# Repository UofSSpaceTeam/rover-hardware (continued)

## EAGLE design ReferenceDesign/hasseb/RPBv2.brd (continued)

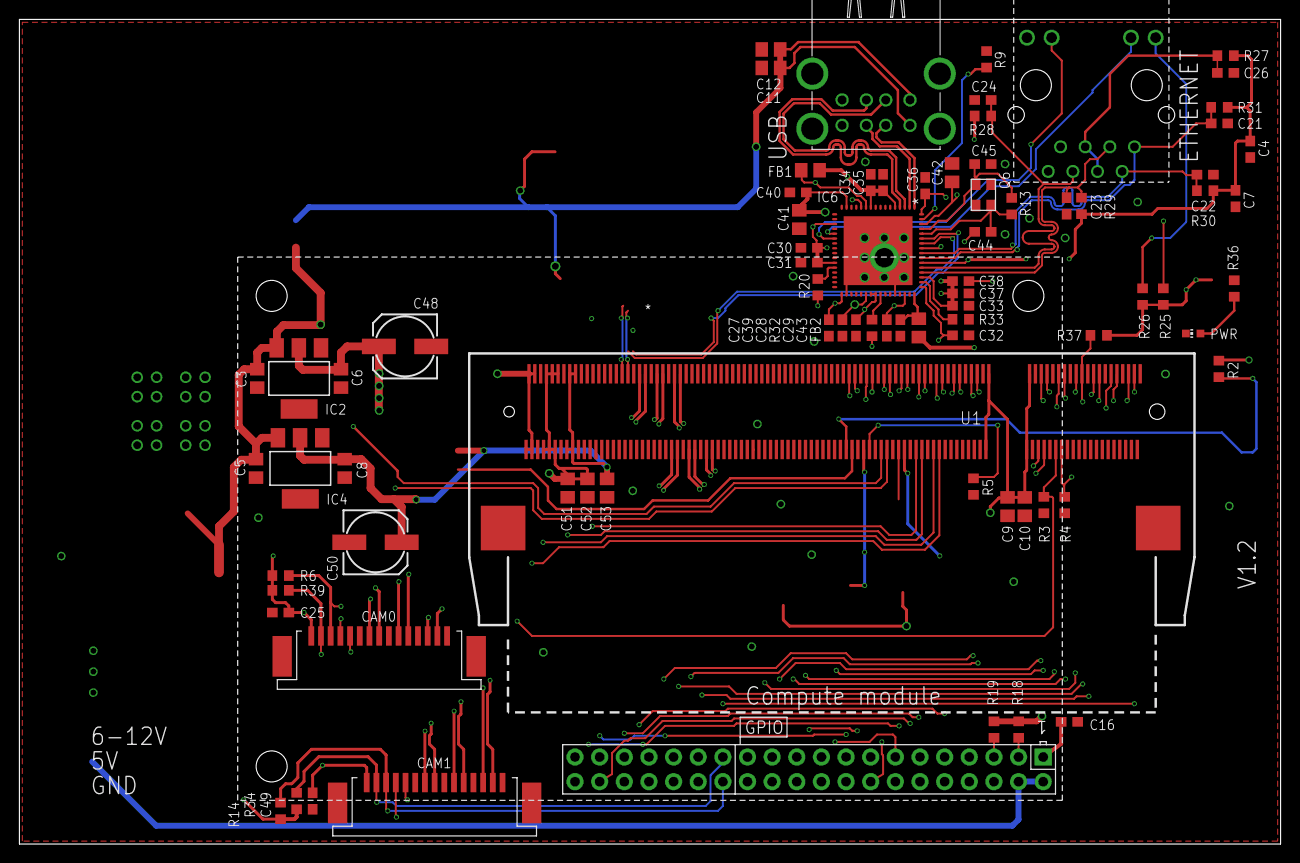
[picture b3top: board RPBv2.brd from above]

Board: 4 copper layers, 130.0 x 85.0 mm, 79 parts (0 on the bottom side), 76 nets.

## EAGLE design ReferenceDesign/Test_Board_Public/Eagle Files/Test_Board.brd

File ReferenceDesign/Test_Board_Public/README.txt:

----This Zip File has been downloaded from http://rpi.pmfg.me

----If you bought these plans from another location other than http://rpi.pmfg.me 
    please get a refund. 

---If you do like the Test Board Please Donate on http://rpi.pmfg.me

---If you do use this Test Board in a Commercial Product. 
   Please Donate from the sales of your product. 
   the world and I will Love you for it.

---This board Comprises of a 4 Layer Board. do not go less than 4 Layers.
   Please see /Eagle Files/Layers_Info.jpg on how the layers should be set. 
   This Must be Accurate as USB and Ethernet Traces have been set to use those Layer settings.

---Please note that the Test Board in its CURRENT Configuration will work!
   This Board has been Tested Extensively before the plans have been made available on the Internet.

---These Plans have been Provided AS IS and As such I will hold no Responsibility if they have been changed
   or an Issue arise from PCB manufacturing or Materials.

---Lastly Please put a mention about me on any product 
   that was derived from this Test Board. 

---if you have any Questions or Queries please post them to the link below. 
   http://www.raspberrypi.org/forums/viewtopic.php?f=98&t=80708

Thank You!

This zip file should contain:
  README.txt (this file)
  /Eagle Files/Test_Board.sch (Eagle CAD Schematic)
  /Eagle Files/Test_Board.brd (Eagle CAD Board File)
  /Eagle Files/Test_Board_BOM.xlsx (Bill of Materials)
  Test_Board_Schematic.pdf (PDF of schematic)
  /GERBERS (Board gerbers)

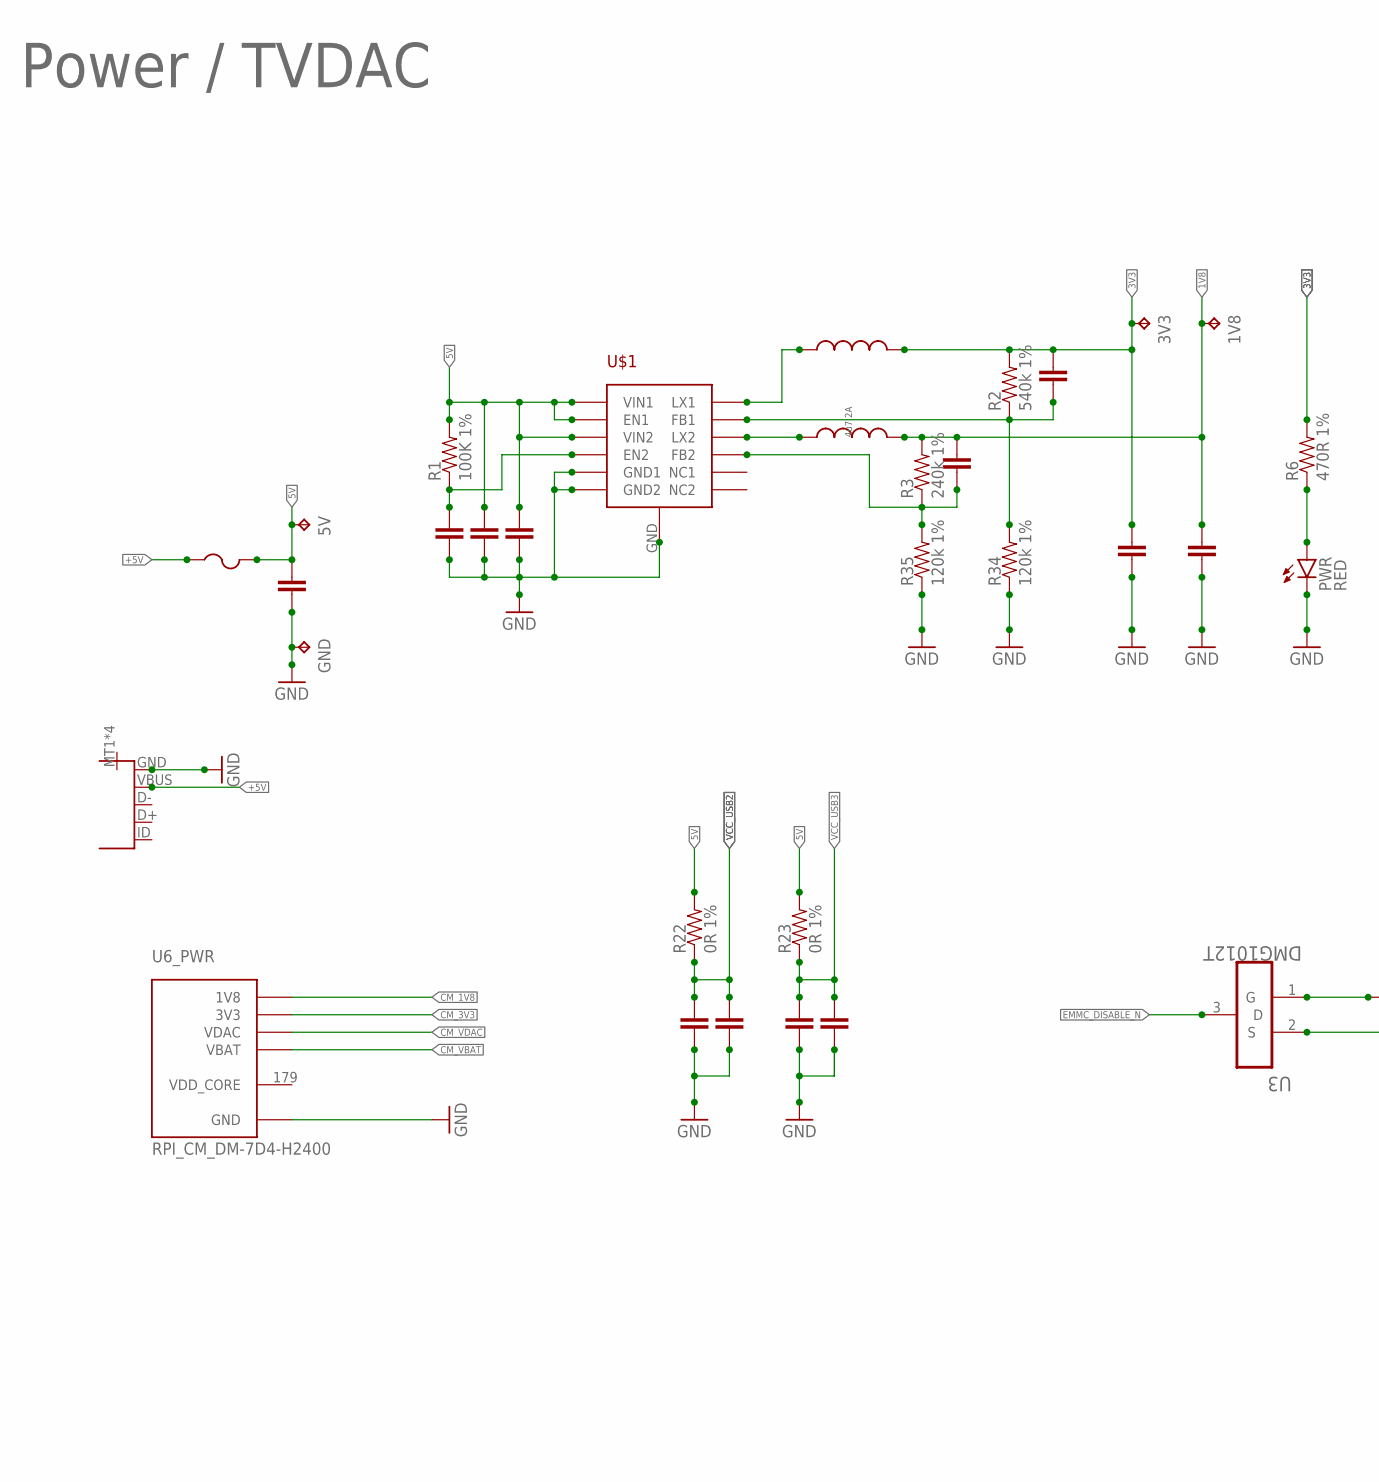
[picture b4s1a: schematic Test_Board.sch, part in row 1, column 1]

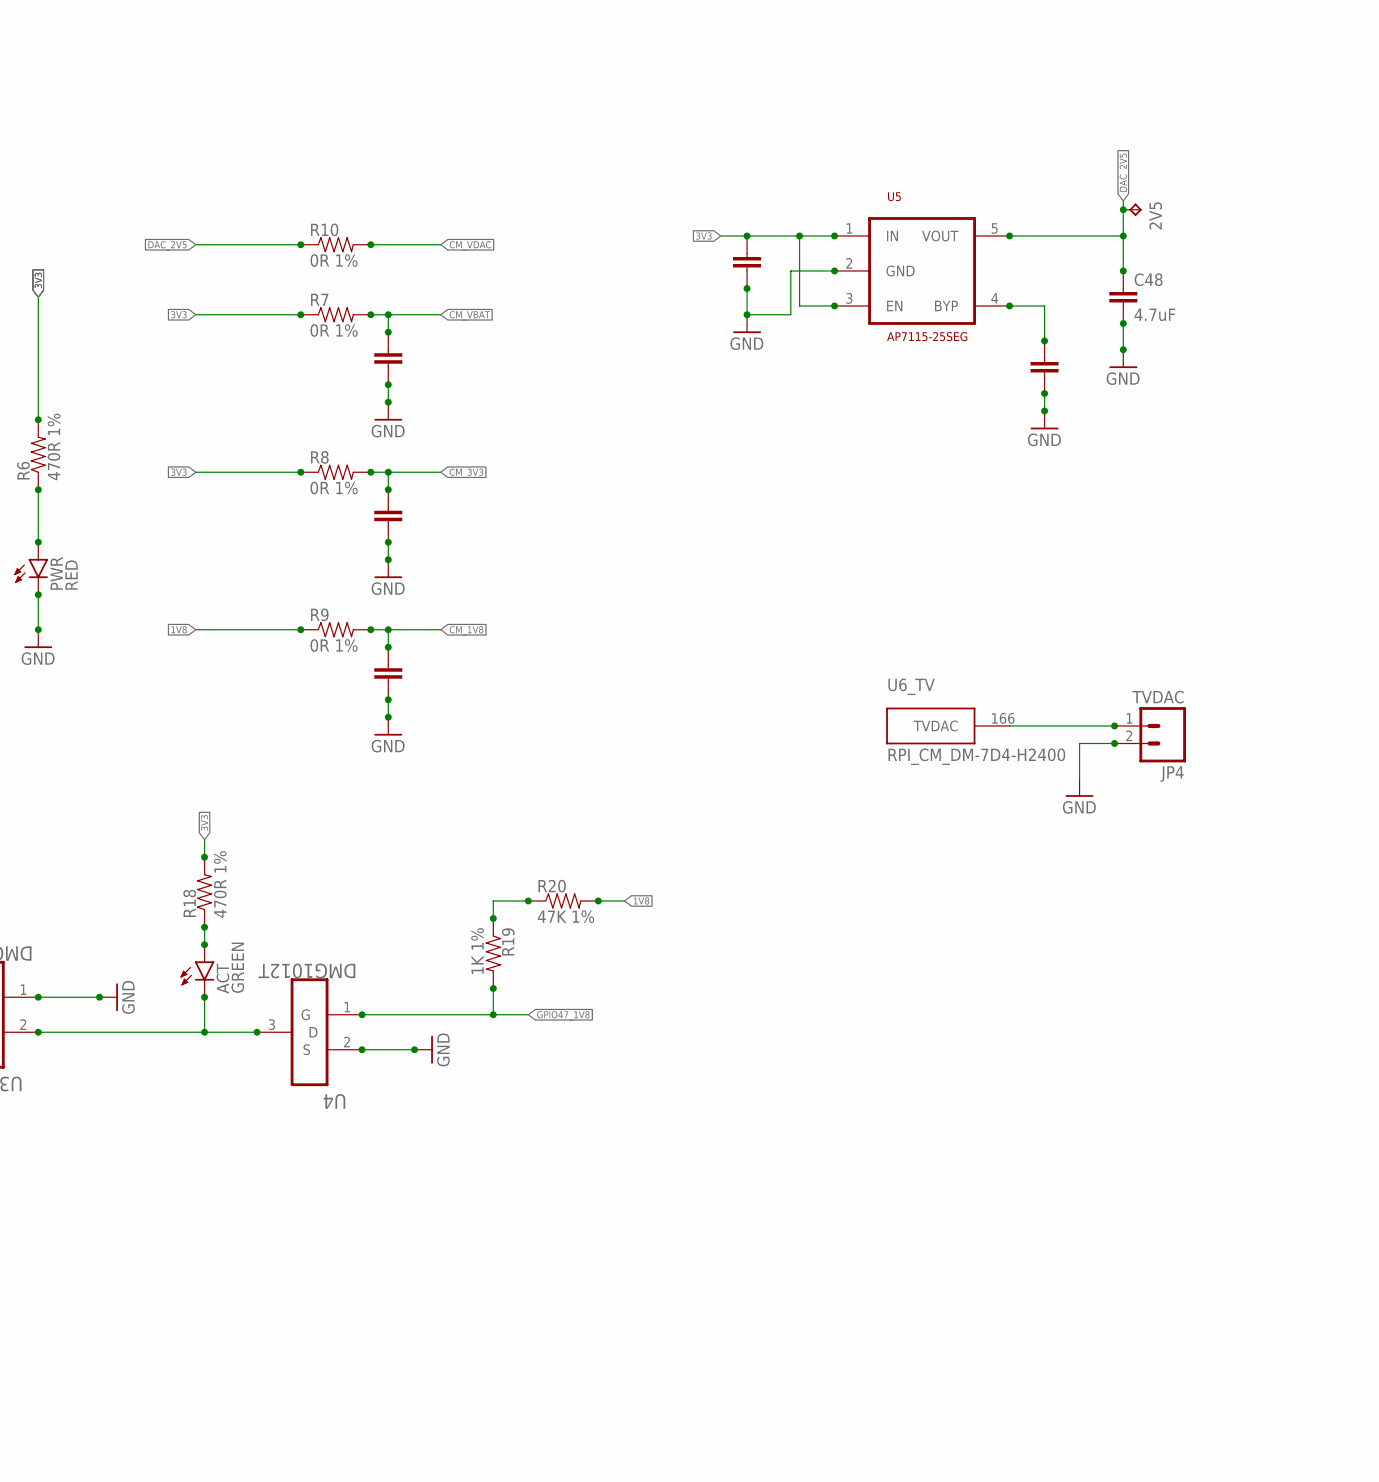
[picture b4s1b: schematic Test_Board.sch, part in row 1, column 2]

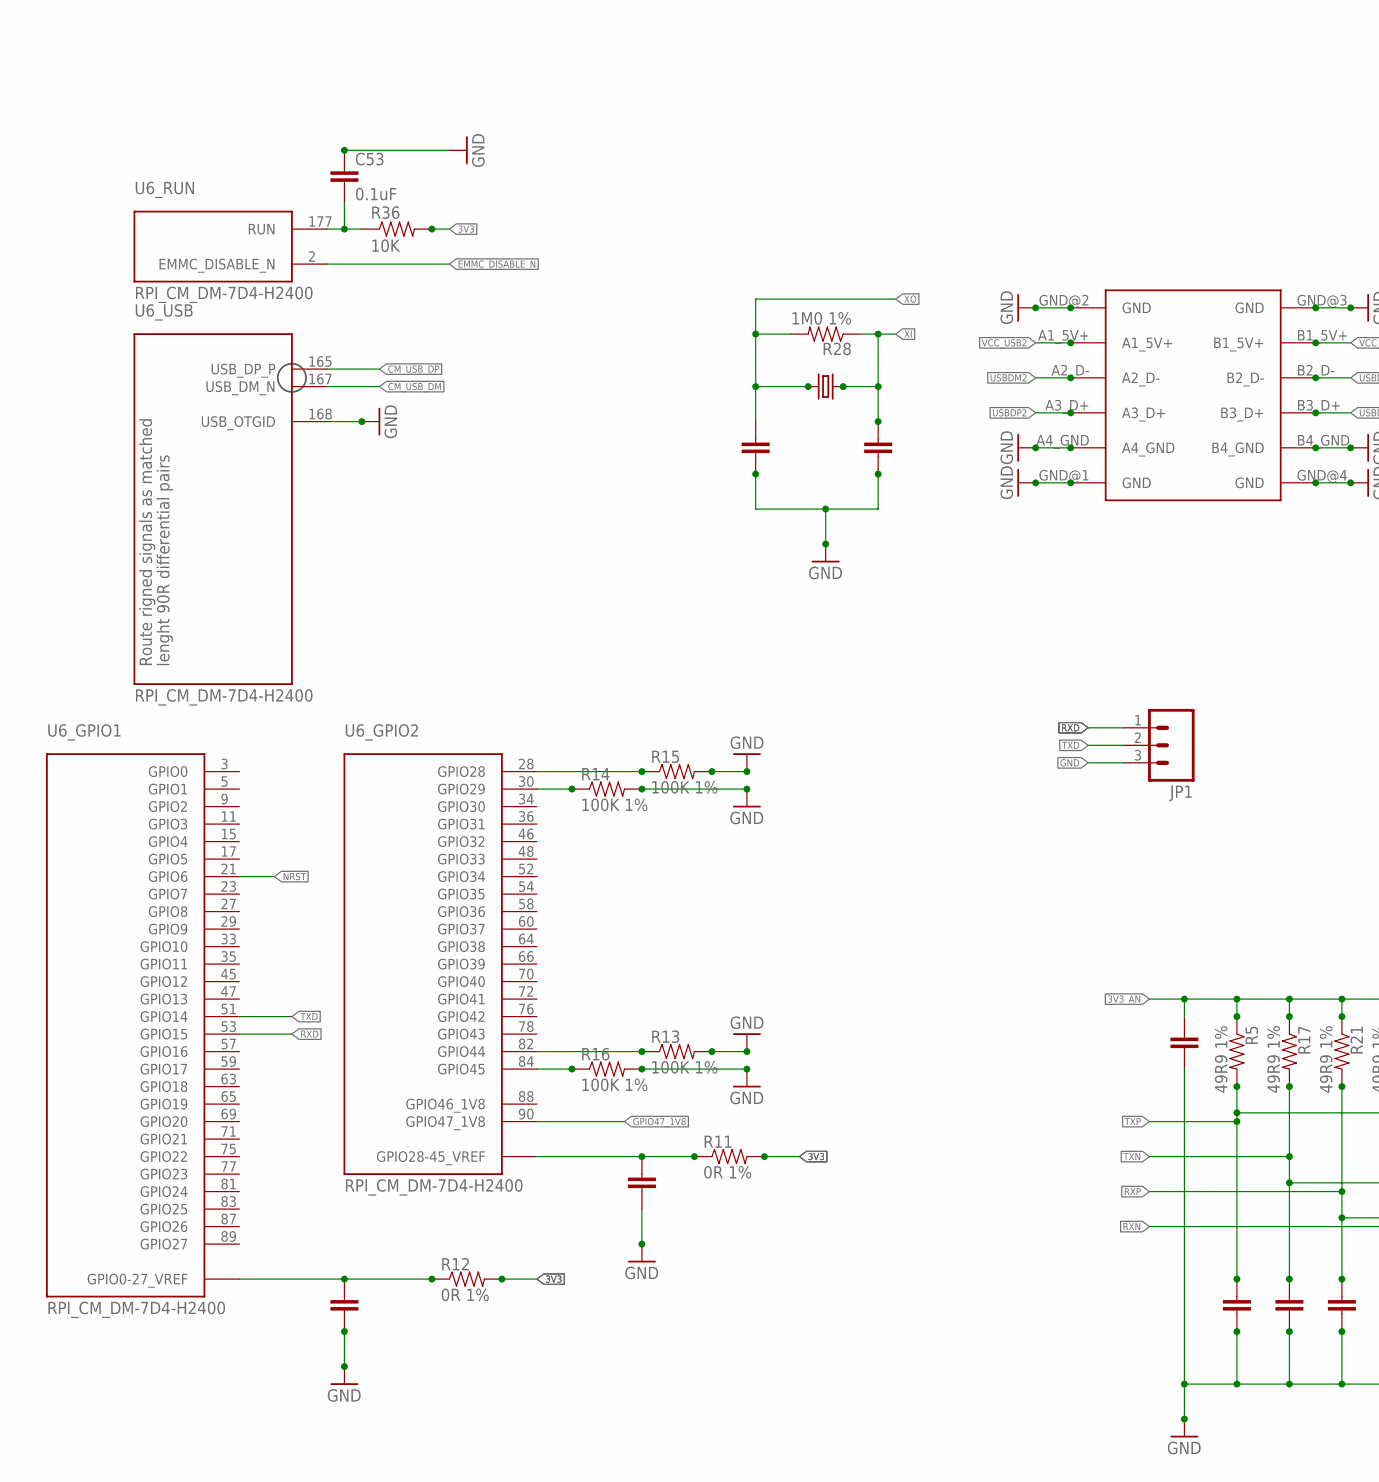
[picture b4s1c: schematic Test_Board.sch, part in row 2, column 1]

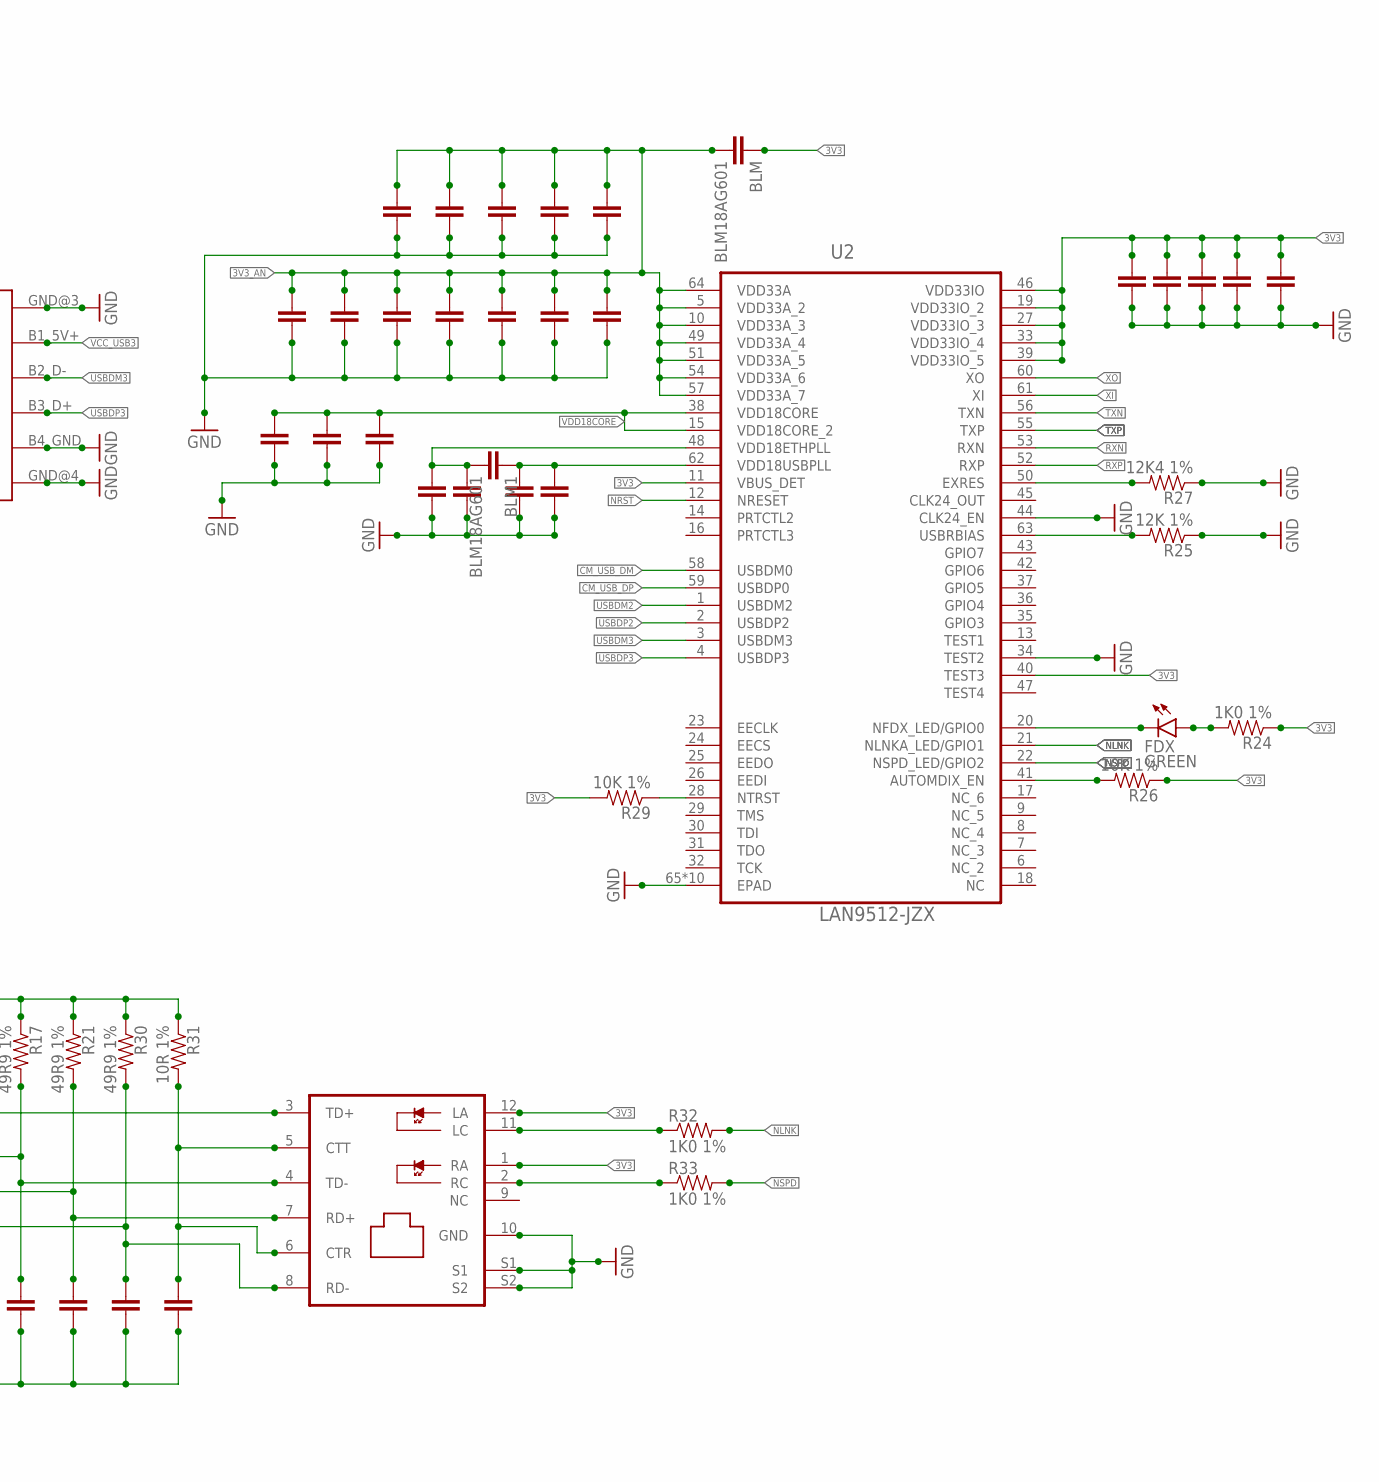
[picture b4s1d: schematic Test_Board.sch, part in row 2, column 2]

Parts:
1V8, 2V5, 3V3, 5V: TPB1,27; B1,27
ACT: GREEN; LED-0603
BLM, BLM1: BLM18AG601; 0603-CAP
C1, C9, C10, C11: 47uF; 1206
C2, C17, C18, C19, C20, C22, C23, C24, C25, C26, C27, C28, C29, C30, C31, C32, C33, C34, C35, C39, C40, C41, C42, C46, C47: 100nF; 0402
C3, C4, C6, C8: 10uF; 0805
C5, C7, C16, C43: 15pf 50V 5%; 0402
C12, C13: 1uf; 0402
C14, C15: 100uF 10v; 1206
C21, C36: 4u7; 0402
C37, C38: 33pf 5%; 0402
C44: 47uf 10v; 0805
C45: 1uF; 0402
C48: 4.7uF; 0603-CAP
C49: 22nF; 0805
C50: 47uF 10V; 0805
C51, C52: 100pF; 0402
C53: 0.1uF; 0603-CAP
F1: PTCFUSE-1812; 1812
FDX: GREEN; LED-0603
GND: TPB1,27; B1,27
J1: J3011; J30
JP1: M03PTH; 1X03
JP3: USB-IDMICRO; USB-MICRO
JP4: TVDAC; 1X02
L1, L2: 4.7u 2A; SRN4018
PWR: RED; LED-0603
R1, R13, R14, R15, R16: 100K 1%; 0402-RES
R2: 540k 1%; 0402-RES
R3: 240k 1%; 0402-RES
R5, R17, R21, R30: 49R9 1%; 0402-RES
R6, R18: 470R 1%; 0402-RES
R7, R8, R9, R10, R11, R12, R22, R23: 0R 1%; 0402-RES
R19: 1K 1%; 0402-RES
R20: 47K 1%; 0402-RES
R24, R32, R33: 1K0 1%; 0402-RES
R25: 12K 1%; 0402-RES
R26, R29: 10K 1%; 0402-RES
R27: 12K4 1%; 0402-RES
R28: 1M0 1%; 0402-RES
R31: 10R 1%; 0402-RES
R34, R35: 120k 1%; 0402-RES
R36: 10K; 0402-RES
U2: LAN9512-JZX; QFN50P900X900X100-65N
U3, U4: DMG1012T; SOT50P160X90-3N
U5: AP7115-25SEG; SOT353
U6: RPI_CM_DM-7D4-H2400; JST-DM-200P
U$1: WDFN-12L
USB1: 72309USB-TYPE-A; 72309
Y1: CRYSTAL5X3; CRYSTAL-SMD-5X3

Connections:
1V8: 1V8.TP, C8.1, C52.1, L2.P$2 (2), R3.2, R9.1, R20.2
3V3: 3V3.TP, BLM.1, C6.1, C21.1, C32.1, C33.1, C34.1, C35.1, C45.1, C51.1, J1.1 (RA), J1.12 (LA), L1.P$2 (2), R2.2, R6.2, R7.1, R8.1, R11.2, R12.2, R18.2, R24.1, R26.1, R29.2, R36.2, U2.11 (VBUS_DET), U2.19 (VDD33IO_2), U2.27 (VDD33IO_3), U2.33 (VDD33IO_4), U2.39 (VDD33IO_5), U2.40 (TEST3), U2.46 (VDD33IO), U5.1 (IN), U5.3 (EN)
3V3_AN: BLM.2, C17.1, C18.1, C19.1, C20.1, C22.1, C23.1, C24.1, C25.1, C26.1, C27.1, C28.1, C29.1, C46.1, R5.1, R17.1, R21.1, R30.1, R31.1, U2.5 (VDD33A_2), U2.10 (VDD33A_3), U2.49 (VDD33A_4), U2.51 (VDD33A_5), U2.54 (VDD33A_6), U2.57 (VDD33A_7), U2.64 (VDD33A)
5V: 5V.TP, C1.1, C3.1, C4.1, F1.2, R1.2, R22.2, R23.2, U$1.1 (VIN2), U$1.6 (EN1), U$1.7 (VIN1)
+5V: F1.1, JP3.VBUS
CM_1V8: C11.1, R9.2, U6.183 (1V8), U6.184 (1V8), U6.185 (1V8), U6.186 (1V8)
CM_3V3: C10.1, R8.2, U6.191 (3V3), U6.192 (3V3), U6.193 (3V3), U6.194 (3V3)
CM_USB_DM: U2.58 (USBDM0), U6.167 (USB_DM_N)
CM_USB_DP: U2.59 (USBDP0), U6.165 (USB_DP_P)
CM_VBAT: C9.1, R7.2, U6.197 (VBAT), U6.198 (VBAT), U6.199 (VBAT), U6.200 (VBAT)
CM_VDAC: R10.2, U6.189 (VDAC), U6.190 (VDAC)
DAC_2V5: 2V5.TP, C48.1, R10.1, U5.5 (VOUT)
EMMC_DISABLE_N: U3.3 (D), U6.2 (EMMC_DISABLE_N)
GND: C1.2, C2.2, C3.2, C4.2, C5.2, C6.2, C7.2, C8.2, C9.2, C10.2, C11.2, C12.2, C13.2, C14.2, C15.2, C16.2, C17.2, C18.2, C19.2, C20.2, C21.2, C22.2, C23.2, C24.2, C25.2, C26.2, C27.2, C28.2, C29.2, C30.2, C31.2, C32.2, C33.2, C34.2, C35.2, C36.2, C37.2, C38.2, C39.2, C40.2, C41.2, C42.2, C43.2, C44.2, C45.2, C46.2, C47.2, C48.2, C49.2, C50.2, C53.1, GND.TP, J1.10 (GND), J1.S1, J1.S2, JP1.3, JP3.GND, JP4.2, PWR.C, R13.2, R14.2, R15.2, R16.2, R25.1, R27.1, R34.1, R35.1, U2.34 (TEST2), U2.44 (CLK24_EN), U2.65 (EPAD), U2.GND@1 (EPAD), U2.GND@2 (EPAD), U2.GND@3 (EPAD), U2.GND@4 (EPAD), U2.GND@5 (EPAD), U2.GND@6 (EPAD), U2.GND@7 (EPAD), U2.GND@8 (EPAD), U2.GND@9 (EPAD), U3.1 (G), U4.2 (S), U5.2 (GND), U6.1 (GND), U6.7 (GND), U6.13 (GND), U6.19 (GND), U6.25 (GND), U6.26 (GND), U6.31 (GND), U6.32 (GND), U6.37 (GND), U6.38 (GND), U6.43 (GND), U6.44 (GND), U6.49 (GND), U6.50 (GND), U6.55 (GND), U6.56 (GND), U6.61 (GND), U6.62 (GND), U6.67 (GND), U6.68 (GND), U6.73 (GND), U6.74 (GND), U6.79 (GND), U6.80 (GND), U6.85 (GND), U6.86 (GND), U6.91 (GND), U6.92 (GND), U6.97 (GND), U6.98 (GND), U6.103 (GND), U6.104 (GND), U6.109 (GND), U6.110 (GND), U6.115 (GND), U6.116 (GND), U6.121 (GND), U6.122 (GND), U6.127 (GND), U6.133 (GND), U6.134 (GND), U6.139 (GND), U6.140 (GND), U6.145 (GND), U6.146 (GND), U6.151 (GND), U6.152 (GND), U6.157 (GND), U6.163 (GND), U6.164 (GND), U6.168 (USB_OTGID), U6.169 (GND), U6.170 (GND), U6.181 (GND), U6.182 (GND), U6.187 (GND), U6.188 (GND), U6.195 (GND), U6.196 (GND), U$1.3 (GND1), U$1.9 (GND2), U$1.GND, USB1.A4_GND, USB1.B4_GND, USB1.GND@1 (GND), USB1.GND@2 (GND), USB1.GND@3 (GND), USB1.GND@4 (GND)
GPI047_CTL_1V8: R19.1, R20.1
GPIO47_1V8: R19.2, U4.1 (G), U6.90 (GPIO47_1V8)
unnamed: L1.P$1 (1), U$1.8 (LX1)
unnamed: C51.2, R2.1, R34.2, U$1.4 (FB1)
unnamed: C2.1, R1.1, U$1.12 (EN2)
unnamed: L2.P$1 (1), U$1.2 (LX2)
unnamed: C12.1, R11.1, U6.41 (GPIO28-45_VREF), U6.42 (GPIO28-45_VREF)
unnamed: C52.2, R3.1, R35.2, U$1.10 (FB2)
unnamed: PWR.A, R6.1
unnamed: C13.1, R12.1, U6.39 (GPIO0-27_VREF), U6.40 (GPIO0-27_VREF)
unnamed: R15.1, U6.28 (GPIO28)
unnamed: R14.1, U6.30 (GPIO29)
unnamed: R13.1, U6.82 (GPIO44)
unnamed: R16.1, U6.84 (GPIO45)
unnamed: FDX.A, R24.2
unnamed: ACT.C, U3.2 (S), U4.3 (D)
unnamed: ACT.A, R18.1
unnamed: R25.2, U2.63 (USBRBIAS)
unnamed: C53.2, R36.1, U6.177 (RUN)
unnamed: JP4.1, U6.166 (TVDAC)
unnamed: C47.1, U5.4 (BYP)
unnamed: BLM1.1, C41.1, C42.1, U2.62 (VDD18USBPLL)
unnamed: BLM1.2, C39.1, C40.1, U2.48 (VDD18ETHPLL)
unnamed: R26.2, U2.41 (AUTOMDIX_EN)
unnamed: R27.2, U2.50 (EXRES)
unnamed: R29.1, U2.28 (NTRST)
unnamed: J1.11 (LC), R32.1
unnamed: J1.2 (RC), R33.1
unnamed: C49.1, J1.5 (CTT), J1.6 (CTR), R31.2
unnamed: FDX.C, U2.20 (NFDX_LED/GPIO0)
NLNK: R32.2, U2.21 (NLNKA_LED/GPIO1)
NRST: U2.12 (NRESET), U6.21 (GPIO6)
NSPD: R33.2, U2.22 (NSPD_LED/GPIO2)
RXD: JP1.1, U6.53 (GPIO15)
RXN: C43.1, J1.8 (RD-), R30.2, U2.53 (RXN)
RXP: C16.1, J1.7 (RD+), R21.2, U2.52 (RXP)
TXD: JP1.2, U6.51 (GPIO14)
TXN: C7.1, J1.4 (TD-), R17.2, U2.56 (TXN)
TXP: C5.1, J1.3 (TD+), R5.2, U2.55 (TXP)
USBDM2: U2.1 (USBDM2), USB1.A2_D-
USBDM3: U2.3 (USBDM3), USB1.B2_D-
USBDP2: U2.2 (USBDP2), USB1.A3_D+
USBDP3: U2.4 (USBDP3), USB1.B3_D+
VCC_USB2: C14.1, C44.1, R22.1, USB1.A1_5V+
VCC_USB3: C15.1, C50.1, R23.1, USB1.B1_5V+
VDD18CORE: C30.1, C31.1, C36.1, U2.15 (VDD18CORE_2), U2.38 (VDD18CORE)
XI: C37.1, R28.1, U2.61 (XI), Y1.3 (2)
XO: C38.1, R28.2, U2.60 (XO), Y1.1

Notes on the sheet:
Power / TVDAC

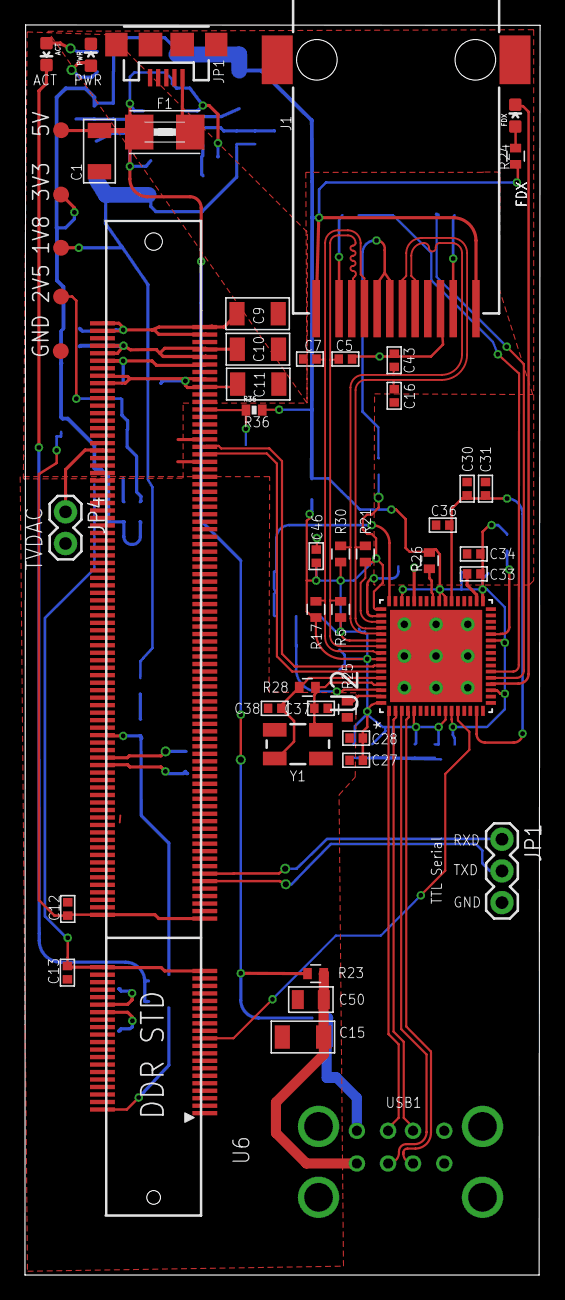
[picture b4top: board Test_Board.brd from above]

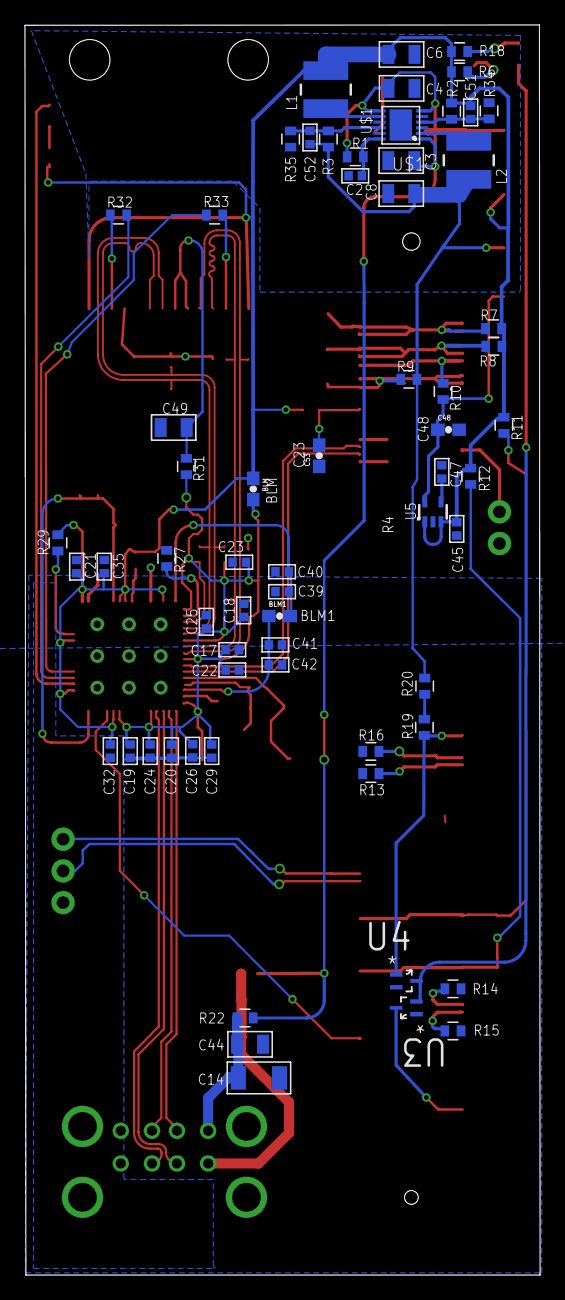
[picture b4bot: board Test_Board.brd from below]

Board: 4 copper layers, 41.3 x 100.2 mm, 113 parts (64 on the bottom side), 62 nets.

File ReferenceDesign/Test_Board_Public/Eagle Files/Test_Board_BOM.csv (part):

"Part";"Value";"Device";"Package";"Description";"DK";"L2";"MN";"MPN";"OC_FARNELL";"OC_NEWARK";"PACKAGE";"PARTNO";"PROD_ID";"SUPPLIER";"TP_SIGNAL_NAME";"VALUE";"VID";
"1V8";"TPB1,27";"TPB1,27";"B1,27";"Test pad";"";"";"";"";"";"";"";"";"";"";"";"";"";
"2V5";"TPB1,27";"TPB1,27";"B1,27";"Test pad";"";"";"";"";"";"";"";"";"";"";"";"";"";
"3V3";"TPB1,27";"TPB1,27";"B1,27";"Test pad";"";"";"";"";"";"";"";"";"";"";"";"";"";
"5V";"TPB1,27";"TPB1,27";"B1,27";"Test pad";"";"";"";"";"";"";"";"";"";"";"";"";"";
"ACT";"GREEN";"LED0603";"LED-0603";"LEDs";"";"";"";"";"";"";"";"";"";"";"";"";"";
"BLM";"BLM18AG601";"0.1UF-25V-5%(0603)";"0603-CAP";"CAP-08604";"";"";"";"";"";"";"";"";"CAP-08604";"";"";"0.1uF";"";
"BLM1";"BLM18AG601";"0.1UF-25V-5%(0603)";"0603-CAP";"CAP-08604";"";"";"";"";"";"";"";"";"CAP-08604";"";"";"0.1uF";"";
"C1";"47uF";"C_1206";"1206";"";"";"";"";"";"";"";"";"";"";"";"";"";"";
"C2";"100nF";"C_0402";"0402";"";"";"";"";"";"";"";"";"";"";"";"";"";"";
"C3";"10uF";"C_0805";"0805";"";"";"";"TDK Corp.";"";"";"";"";"C2012X5R1Cxxxxxxx";"";"";"";"";"DK";
"C4";"10uF";"C_0805";"0805";"";"";"";"TDK Corp.";"";"";"";"";"C2012X5R1Cxxxxxxx";"";"";"";"";"DK";
"C5";"15pf 50V 5%";"C_0402";"0402";"";"";"";"";"";"";"";"";"";"";"";"";"";"";
"C6";"10uF";"C_0805";"0805";"";"";"";"TDK Corp.";"";"";"";"";"C2012X5R1Cxxxxxxx";"";"";"";"";"DK";
"C7";"15pf 50V 5%";"C_0402";"0402";"";"";"";"";"";"";"";"";"";"";"";"";"";"";
"C8";"10uF";"C_0805";"0805";"";"";"";"TDK Corp.";"";"";"";"";"C2012X5R1Cxxxxxxx";"";"";"";"";"DK";
"C9";"47uF";"C_1206";"1206";"";"";"";"";"";"";"";"";"";"";"";"";"";"";
"C10";"47uF";"C_1206";"1206";"";"";"";"";"";"";"";"";"";"";"";"";"";"";
"C11";"47uF";"C_1206";"1206";"";"";"";"";"";"";"";"";"";"";"";"";"";"";
"C12";"1uf";"C_0402";"0402";"";"";"";"";"";"";"";"";"";"";"";"";"";"";
"C13";"1uf";"C_0402";"0402";"";"";"";"";"";"";"";"";"";"";"";"";"";"";
"C14";"100uF 10v";"C_1206";"1206";"";"";"";"";"";"";"";"";"";"";"";"";"";"";
"C15";"100uF 10v";"C_1206";"1206";"";"";"";"";"";"";"";"";"";"";"";"";"";"";
"C16";"15pf 50V 5%";"C_0402";"0402";"";"";"";"";"";"";"";"";"";"";"";"";"";"";
"C17";"100nF";"C_0402";"0402";"";"";"";"";"";"";"";"";"";"";"";"";"";"";
"C18";"100nF";"C_0402";"0402";"";"";"";"";"";"";"";"";"";"";"";"";"";"";
"C19";"100nF";"C_0402";"0402";"";"";"";"";"";"";"";"";"";"";"";"";"";"";
"C20";"100nF";"C_0402";"0402";"";"";"";"";"";"";"";"";"";"";"";"";"";"";
"C21";"4u7";"C_0402";"0402";"";"";"";"";"";"";"";"";"";"";"";"";"";"";
"C22";"100nF";"C_0402";"0402";"";"";"";"";"";"";"";"";"";"";"";"";"";"";
"C23";"100nF";"C_0402";"0402";"";"";"";"";"";"";"";"";"";"";"";"";"";"";
"C24";"100nF";"C_0402";"0402";"";"";"";"";"";"";"";"";"";"";"";"";"";"";
"C25";"100nF";"C_0402";"0402";"";"";"";"";"";"";"";"";"";"";"";"";"";"";
"C26";"100nF";"C_0402";"0402";"";"";"";"";"";"";"";"";"";"";"";"";"";"";
"C27";"100nF";"C_0402";"0402";"";"";"";"";"";"";"";"";"";"";"";"";"";"";
"C28";"100nF";"C_0402";"0402";"";"";"";"";"";"";"";"";"";"";"";"";"";"";
"C29";"100nF";"C_0402";"0402";"";"";"";"";"";"";"";"";"";"";"";"";"";"";
"C30";"100nF";"C_0402";"0402";"";"";"";"";"";"";"";"";"";"";"";"";"";"";
"C31";"100nF";"C_0402";"0402";"";"";"";"";"";"";"";"";"";"";"";"";"";"";
"C32";"100nF";"C_0402";"0402";"";"";"";"";"";"";"";"";"";"";"";"";"";"";
"C33";"100nF";"C_0402";"0402";"";"";"";"";"";"";"";"";"";"";"";"";"";"";
"C34";"100nF";"C_0402";"0402";"";"";"";"";"";"";"";"";"";"";"";"";"";"";
"C35";"100nF";"C_0402";"0402";"";"";"";"";"";"";"";"";"";"";"";"";"";"";
"C36";"4u7";"C_0402";"0402";"";"";"";"";"";"";"";"";"";"";"";"";"";"";
"C37";"33pf 5%";"C_0402";"0402";"";"";"";"";"";"";"";"";"";"";"";"";"";"";
"C38";"33pf 5%";"C_0402";"0402";"";"";"";"";"";"";"";"";"";"";"";"";"";"";
"C39";"100nF";"C_0402";"0402";"";"";"";"";"";"";"";"";"";"";"";"";"";"";
"C40";"100nF";"C_0402";"0402";"";"";"";"";"";"";"";"";"";"";"";"";"";"";
"C41";"100nF";"C_0402";"0402";"";"";"";"";"";"";"";"";"";"";"";"";"";"";
"C42";"100nF";"C_0402";"0402";"";"";"";"";"";"";"";"";"";"";"";"";"";"";
"C43";"15pf 50V 5%";"C_0402";"0402";"";"";"";"";"";"";"";"";"";"";"";"";"";"";
"C44";"47uf 10v";"C_0805";"0805";"";"";"";"TDK Corp.";"";"";"";"";"C2012X5R1Cxxxxxxx";"";"";"";"";"DK";
"C45";"1uF";"C_0402";"0402";"";"";"";"";"";"";"";"";"";"";"";"";"";"";
"C46";"100nF";"C_0402";"0402";"";"";"";"";"";"";"";"";"";"";"";"";"";"";
"C47";"100nF";"C_0402";"0402";"";"";"";"";"";"";"";"";"";"";"";"";"";"";
"C48";"4.7uF";"4.7UF-6.3V-10%(0603)0603";"0603-CAP";"CAP-08280";"";"";"";"";"";"";"";"";"CAP-08280";"";"";"4.7uF";"";
"C49";"22nF";"C_0805";"0805";"";"";"";"TDK Corp.";"";"";"";"";"C2012X5R1Cxxxxxxx";"";"";"";"";"DK";
"C50";"47uF 10V";"C_0805";"0805";"";"";"";"TDK Corp.";"";"";"";"";"C2012X5R1Cxxxxxxx";"";"";"";"";"DK";
"C51";"100pF";"C_0402";"0402";"";"";"";"";"";"";"";"";"";"";"";"";"";"";
"C52";"100pF";"C_0402";"0402";"";"";"";"";"";"";"";"";"";"";"";"";"";"";
"C53";"0.1uF";"0.1UF-25V-5%(0603)";"0603-CAP";"CAP-08604";"";"";"";"";"";"";"";"";"CAP-08604";"";"";"0.1uF";"";
"F1";"";"PTCFUSE-1812";"1812";"";"";"";"";"";"";"";"";"";"";"";"";"";"";
"FDX";"GREEN";"LED0603";"LED-0603";"LEDs";"";"";"";"";"";"";"";"";"";"";"";"";"";
"GND";"TPB1,27";"TPB1,27";"B1,27";"Test pad";"";"";"";"";"";"";"";"";"";"";"";"";"";
"J1";"J3011";"J3011";"J30";"";"";"";"";"";"";"";"";"";"";"";"";"";"";
"JP1";"";"M03PTH";"1X03";"Header 3";"";"";"";"";"";"";"";"";"";"";"";"";"";
"JP3";"USB-IDMICRO";"USB-IDMICRO";"USB-MICRO";"";"";"";"";"";"";"";"";"";"CONN-09505";"";"";"";"";
"JP4";"TVDAC";"M02PTH";"1X02";"Standard 2-pin 0.1" header. Use with";"";"";"";"";"";"";"";"";"";"";"";"";"";
"L1";"4.7u 2A";"INDUCTOR-SRN4018";"SRN4018";"";"";"";"";"";"";"";"";"";"";"";"";"";"";
"L2";"4.7u 2A";"INDUCTOR-SRN4018";"SRN4018";"";"";"4u7 2A";"";"";"";"";"";"";"";"";"";"";"";
"PWR";"RED";"LED0603";"LED-0603";"LEDs";"";"";"";"";"";"";"";"";"";"";"";"";"";
"R1";"100K 1%";"RESISTOR0402-RES";"0402-RES";"";"";"";"";"";"";"";"";"";"";"";"";"";"";
"R2";"540k 1%";"RESISTOR0402-RES";"0402-RES";"";"";"";"";"";"";"";"";"";"";"";"";"";"";
"R3";"240k 1%";"RESISTOR0402-RES";"0402-RES";"";"";"";"";"";"";"";"";"";"";"";"";"";"";
"R5";"49R9 1%";"RESISTOR0402-RES";"0402-RES";"";"";"";"";"";"";"";"";"";"";"";"";"";"";
"R6";"470R 1%";"RESISTOR0402-RES";"0402-RES";"";"";"";"";"";"";"";"";"";"";"";"";"";"";
"R7";"0R 1%";"RESISTOR0402-RES";"0402-RES";"";"";"";"";"";"";"";"";"";"";"";"";"";"";
"R8";"0R 1%";"RESISTOR0402-RES";"0402-RES";"";"";"";"";"";"";"";"";"";"";"";"";"";"";
"R9";"0R 1%";"RESISTOR0402-RES";"0402-RES";"";"";"";"";"";"";"";"";"";"";"";"";"";"";
"R10";"0R 1%";"RESISTOR0402-RES";"0402-RES";"";"";"";"";"";"";"";"";"";"";"";"";"";"";
"R11";"0R 1%";"RESISTOR0402-RES";"0402-RES";"";"";"";"";"";"";"";"";"";"";"";"";"";"";
"R12";"0R 1%";"RESISTOR0402-RES";"0402-RES";"";"";"";"";"";"";"";"";"";"";"";"";"";"";
"R13";"100K 1%";"RESISTOR0402-RES";"0402-RES";"";"";"";"";"";"";"";"";"";"";"";"";"";"";
"R14";"100K 1%";"RESISTOR0402-RES";"0402-RES";"";"";"";"";"";"";"";"";"";"";"";"";"";"";
"R15";"100K 1%";"RESISTOR0402-RES";"0402-RES";"";"";"";"";"";"";"";"";"";"";"";"";"";"";
"R16";"100K 1%";"RESISTOR0402-RES";"0402-RES";"";"";"";"";"";"";"";"";"";"";"";"";"";"";
"R17";"49R9 1%";"RESISTOR0402-RES";"0402-RES";"";"";"";"";"";"";"";"";"";"";"";"";"";"";
"R18";"470R 1%";"RESISTOR0402-RES";"0402-RES";"";"";"";"";"";"";"";"";"";"";"";"";"";"";
"R19";"1K 1%";"RESISTOR0402-RES";"0402-RES";"";"";"";"";"";"";"";"";"";"";"";"";"";"";
"R20";"47K 1%";"RESISTOR0402-RES";"0402-RES";"";"";"";"";"";"";"";"";"";"";"";"";"";"";
"R21";"49R9 1%";"RESISTOR0402-RES";"0402-RES";"";"";"";"";"";"";"";"";"";"";"";"";"";"";
"R22";"0R 1%";"RESISTOR0402-RES";"0402-RES";"";"";"";"";"";"";"";"";"";"";"";"";"";"";
"R23";"0R 1%";"RESISTOR0402-RES";"0402-RES";"";"";"";"";"";"";"";"";"";"";"";"";"";"";
"R24";"1K0 1%";"RESISTOR0402-RES";"0402-RES";"";"";"";"";"";"";"";"";"";"";"";"";"";"";
"R25";"12K 1%";"RESISTOR0402-RES";"0402-RES";"";"";"";"";"";"";"";"";"";"";"";"";"";"";
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
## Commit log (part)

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2015-06-13 existing altium files
2015-06-20 Total Reorganization for GitHub
2015-06-20 Added all files back
2015-06-21 Added ArmBoard project from Liam
2015-06-21 Ummm not sure why it broke :)
2015-06-21 hmmm
2015-06-21 Test again!
2015-09-11 Cleaned out in preparation for KiCAD
    Removed all files (saved in release) and added a .gitignore
2015-09-15 Added Edison project files
    Testing github commit of KiCad projects
2015-09-15 Added USST Library and linked it to the project
2015-10-10 Dimensions that Austin, Seamus and I were talking about
2015-11-06 Added comprehensive list of libraries with 3D parts!
    Sorry about the size... :O
2015-11-09 Created PI CM Footprint
    Wowza 200 pins. Hope we need all of them! ;)
2015-11-12 Missed a file from last commit
2015-11-12 Nearly done module schematics
    ToDo: Make the footprints for custom parts and layout!
2015-11-13 More routing
    Might start traces over. :page_facing_up:
2015-11-14 Redoing traces
2015-11-14 Redone some routing - nearly finished!
    There's a lot of room for improvement on the digital side.
2015-11-23 Lots of good progress on routing drive PCB
    just a few traces and organization left
2015-11-24 More PCB layout cleaning for Drive PCB
2015-12-23 Added LAN to Pi board
2015-12-27 Added MCP2515 chip to libs
2016-01-02 Added schematics for the arm board.
2016-01-02 Arm Board: Add selector for quadrature encoders
2016-01-07 Arm Board: Added multiplexers for underflow/overflow signals on motors.
2016-01-09 Added a part
2016-01-09 Added lots more to modules!
2016-01-11 Created the ATX Connector
    Located in the “TomParts” Library
2016-01-11 Added a Vcc and a GND to the diagram
2016-01-14 Arm Board: Finish schematic
2016-01-30 Arm Board: added reset lines and fixed various errors
2016-02-18 Arm Board: bug fixes, and added footprints
2016-03-05 Arm Board: finalizing footprints.
2016-03-19 Added PI CM IO "shield"
2016-03-19 Re-Added Power Board Files!
    Had to delete them because of some odd github error
2016-04-02 foo2
2016-04-09 Arm Board: changed optocouplers
2016-04-18 Arm Board: finish pcb layout, make gerbers
2016-04-18 Arm Board: made gerber zip file
2016-04-20 Major updates for power distribution and Communications boards
2016-04-20 Fixed Via Sizes
    Need to get gerbers. I do not have the template Carl used!
2016-04-28 Add arm MCU breakout board
2016-04-28 Arm Breakout: Add pdf of schematic
2016-04-29 Arm Breakout: made pcb layout
2016-04-29 Merging Carl's Changes!
2016-05-13 Updated arm board footprints. Did NOT update pcb layout.
2016-05-21 Notes on inverse lkinematics
2016-09-24 Added Pi CM new Schematics
2016-09-24 Added USB Hub
2016-10-25 Added VESC files for HW v4.12 to projects folder to make changes
2016-12-24 Added USB hub files that were sent to OSHPark
2016-12-24 Added slight schematic change to VESC (not significant)
2016-12-26 Added custom Teensy 3.1/3.2 board.
2016-12-27 Started work on cleaning up FE1.1s USB hub and VESC backplane
2016-12-27 Changed a part as demonstration
2016-12-27 Generalizing symbols used
2016-12-27 PCB Footprints: USB and Motor controller connector
2016-12-30 More schematic updates for VESC
2017-01-05 VESC MOSFET layout
2017-01-07 more VESC card cleanup - still need to fix ground planes, via stiching, and silkscreen
2017-01-07 Added USB hub to backplane
2017-01-07 Added stuff to VESC_Card_Backplane
2017-01-08 Partially did motorcontroller part of schematic
2017-01-12 Updated subsheets and added CAN bus :)
2017-01-13 Commit to save
2017-01-13 Pretty much done 'zzzz'
2017-01-14 Footprint assoc. for backplane
2017-01-14 Fixed backplane slot orientation
2017-01-14 Upload USB hub design as ordered
2017-01-19 Updated card slot dimensions for VESC-R
2017-01-20 Comleted VESC Backplane
2017-01-21 Connected all for VESC_Card_Breakout
2017-01-22 Rotated component
2017-01-26 Outline lines added in. PCB finished :D
2017-01-28 Trying to replace current resistors with surface mount resistors
2017-01-28 Updated Power Distribution Board and refs
2017-02-03 Finished connecting the components, just need to fix copper zones
2017-02-03 Added a copper zone
2017-02-11 added notes for layout of the power board
2017-02-18 Almost done just need to add silk screen stuff
2017-02-22 edited VESC Card Breakout, redid footprint
2017-03-04 Fixed VESC Readme
2017-03-04 ...OK now I fixed it :)
2017-03-25 added BOM for backplane
2017-03-26 More organization of CMIO board
2017-04-01 Added ACS712 Testing Project
2017-04-13 added differential routes
2017-04-15 small change to test slack webhooks
2017-05-02 Added VESC-X Hub project
2017-05-06 Completed schematics and layout of VESC-X Hub
2017-05-06 Cleaned up and tweaked power board to include Aux 12v regulator and current sensor bypass
2017-05-06 forgot to save a file :)
2017-05-11 edited hub board to not look like a panelized design, created gerbers
2017-05-14 Small fixes to commands for pushing all HW repos together
2017-05-15 Added BOMs for ordering using Boms-Away
2017-06-09 Added BNO055 project
2017-06-09 Finished first draft of BNO055 PCB Schematic
2017-06-12 Finished first draft of the BNO055 custom PCB
2017-06-14 Added BNO055 Gerbers for order
2017-09-30 BLDC motor datasheet
2017-11-15 ATmega16HVB Battery Manager IC
    Circuit for battery management and protection.
2017-11-15 Datasheets Pertaining to Batt Management
    Datasheets for battery management components
2018-01-20 Started schematic
2018-01-27 Added on to Schematic
2018-02-03 Added d21 rocket board
2018-02-07 added BOM files from BNO design, early summer 2017
2018-02-08 Edited & re-associated schematic. Replaced 10 pin Molex connector with 8 pin
2018-02-09 finished schematic & started board layout for minipcbPanel
2018-02-10 added onto schematic
2018-02-11 Finished Board Layout
2018-02-11 Rendered Gerbers for pcbPanel
2018-02-12 Added USB3 to schematic. Finished GERBER Files
2018-02-15 Modified schemetic
2018-02-15 Added miniPCB drl file in DXF format(hopefully...)
2018-02-15 Significantly reduced size of the PCB board
2018-02-18 Added new pcb for battery enclosure
2018-03-03 Organized datasheet folder
2018-03-04 PowerBoard V3
2018-03-08 Increased trace width on molex connectors
2018-03-08 Powerboard V3, Notes in the logbook
2018-03-08 Hierarchy Schematic
2018-03-09 Added High Power Schematic
    Added power Transistors
2018-03-09 Clean Up of Schematic
2018-03-09 Added changes to LowPowerSchematic
2018-03-09 Small Changes
2018-03-10 Changed DSH to DSG and added initials to logs
2018-03-10 Worked on LPC, More infor in Log
2018-03-10 Random
2018-03-10 Added 9V Power Supply
2018-03-10 Changed Global vars to hierarchical
2018-03-10 Hierarchical Pins Placed in LowPowerCircuit
2018-03-10 Created top level connections
2018-03-11 Added footprints
    Created BOM for parts, linked footprints to schematic elements
2018-03-11 modified miniPCB board to accomodate 10A current in motor winding traces
2018-03-12 Deleted Barrel Jack Connectors
2018-03-15 Added gerbers for each of the side boards
2018-03-15 Slight changes to PCB panel
2018-03-18 Finishing touches before netlist
2018-03-22 Added silkscreen for 2x4 molex connectors
2018-03-22 added log
2018-03-24 Adding battery enclosure pcb, wedges with 6 screws each
2018-03-24 modified batterymount4 pads to be on front copper
2018-03-24 Lots of changes to the board layout
2018-03-24 Added info to logbook
2018-03-29 worked on Powerboard PCBnew comments in logbook
2018-03-29 Added to Log
2018-04-04 only 6 connections left on PowerBoardV3
2018-04-04 Added Arm Power Board project
2018-04-04 Finishing up PowerBoardV3
2018-04-07 Edit Arm power board
2018-04-07 ADDED LABELS AND CHECKED TRACE WIDTHS
2018-04-09 Adjusting hole distances of wedge pads
2018-04-09 changed the top terminal block footprint
2018-04-09 Vertical connector added
2018-04-09 Changed the 9v terminal block to vertical
2018-04-09 Properly labeled + and - for the arm output connector
2018-04-10 Slight refactor of Side connector board(mounting holes, overall size)
2018-04-10 finished refactor of pcb panels for Electrical Tray. Ready for ordering
2018-04-10 A lot of changes following realization of thickness constraints
2018-04-13 Adjusted capacitor prices a bit
2018-04-14 added/modified mounting holes. Generated Gerbers
2018-04-16 BOM for Arm Powerboard
2018-04-16 Modified Gerber files
2018-04-21 Furthered dev of the front & back panel designs
2018-04-21 Generated final Gerbers/Drill files
2018-04-22 zipped GERBER files bc i forgot to a minute ago
2018-04-23 Finished Back connector board to account for RPi cams
2018-04-23 Updated prices & amounts for components in powerboard BOM
2018-04-25 Made the Arm PCB
2018-04-25 Added resistor to BOM
2018-04-25 added screw holes to arm power board
2018-04-26 Made some minor changes
2018-04-26 regenerated gerber file and drill file of BatteryMount4
2018-04-29 added usb3.0 adpater to arm board
2018-04-29 usb3.0 wired
2018-04-29 finish: adding usb3.0 adapter
2018-04-30 Added Zipped GERBER files bc I forgot... again
2018-05-07 Updated PowerBoardV3 BoM to reflect what we currently have in stock
2018-05-16 The on/off switch is conncted to power
2018-05-16 ARM POWER
2018-05-16 fixed folder organization
2018-05-16 Finished Schematic & Netlist for APB. TK
2018-05-16 Finished & rendered APBv2, updated all BOMs. TK
2018-06-01 added datasheet for LiFe/LiPo batt charger
2018-06-23 added notes
2018-06-23 New Power Board Folder
2018-06-23 Made a new BOM for V4
2018-06-23 Added stuff to V4
2018-06-30 editted R18 footprint and double checked Q1 and Q2 footprints
2018-07-03 Started science 2018 schematic
2018-07-10 modified the PowerBoard V4 schematic, left a comment by the usb connector
2018-07-11 more adjustments to PowerBoard V4
2018-07-11 added 5V 4A DC/DC Power Supply to BOM
2018-07-14 Complete 1st draft for power board v4
2018-07-21 Fixing unconnected connections, added 5V connections
2018-07-23 Small cosmetic changes
2018-07-23 Refactored the fill zones to not be so massive, used up more free space to make board smaller where possible. Didn't change the general organization
2018-07-24 Updated BOM
2018-07-24 Did some more stuff
2018-07-24 Finished updated BOM, added links to completed Digikey/Arrow carts. Will review what we have in stock tomorrow before placing order
2018-07-25 Moved 12V around, small refactor of other connector/comp placement, organized drill holes, generated & zipped all GERBER files. Should be ready for order. TK
2018-07-25 Fixed Schem & Layout so that extra 5/12V conns have same +/- pinout as ones from PowerBoardV2, so that we can use the connectors interchangably. TK
2018-07-26 fixed the spelling of my name
2018-08-08 Added datasheet for Bomb Bot Arm Motors. Thanks Seamus!
2018-08-16 Add files via upload
    Info for the new cables, connectors, junction boxes, etc
2018-08-16 Added a motor and camera spec
2018-08-16 Re-organizing of the folder structure
2018-08-17 Added a couple more things to the Master BOM
2018-08-17 Added a couple lines to the USB sheet
2018-08-20 Created first draft of schematics using USST title block
2018-08-21 Added to the agenda
2018-08-21 Added motor controller project
2018-08-23 Added a connector and crimper
2018-08-27 Adding a couple lines
2018-09-07 Meeting minutes
2018-09-23 added male receptacles for USB and I2C
2018-09-23 Projects that had interest
2018-10-12 I added my name to the rover wiring project
2018-10-16 More Datasheets
2018-11-25 testing out gitbash commits, added BOM_PowerBoard_v5.xlsx
2018-11-26 added minirover kicad project and BOM to repository, added PowerBoard V5 kicad project
2018-12-02 Wireless MCU datasheet
2019-01-07 Created the schematic for the motor driver
    Need to do more research into the microcontroller and if its possible to place arduino on it before implementing it into the schematic.
2019-01-21 Updated Power Board BOM
2019-01-26 Worked on Arm BOM
2019-01-26 Actual Arm board
2019-02-02 Started work on PCB Layout, still want to check if I2C onto the JST connector is possible/useful.
2019-02-09 Added three screw holes, position was just wherever felt free
